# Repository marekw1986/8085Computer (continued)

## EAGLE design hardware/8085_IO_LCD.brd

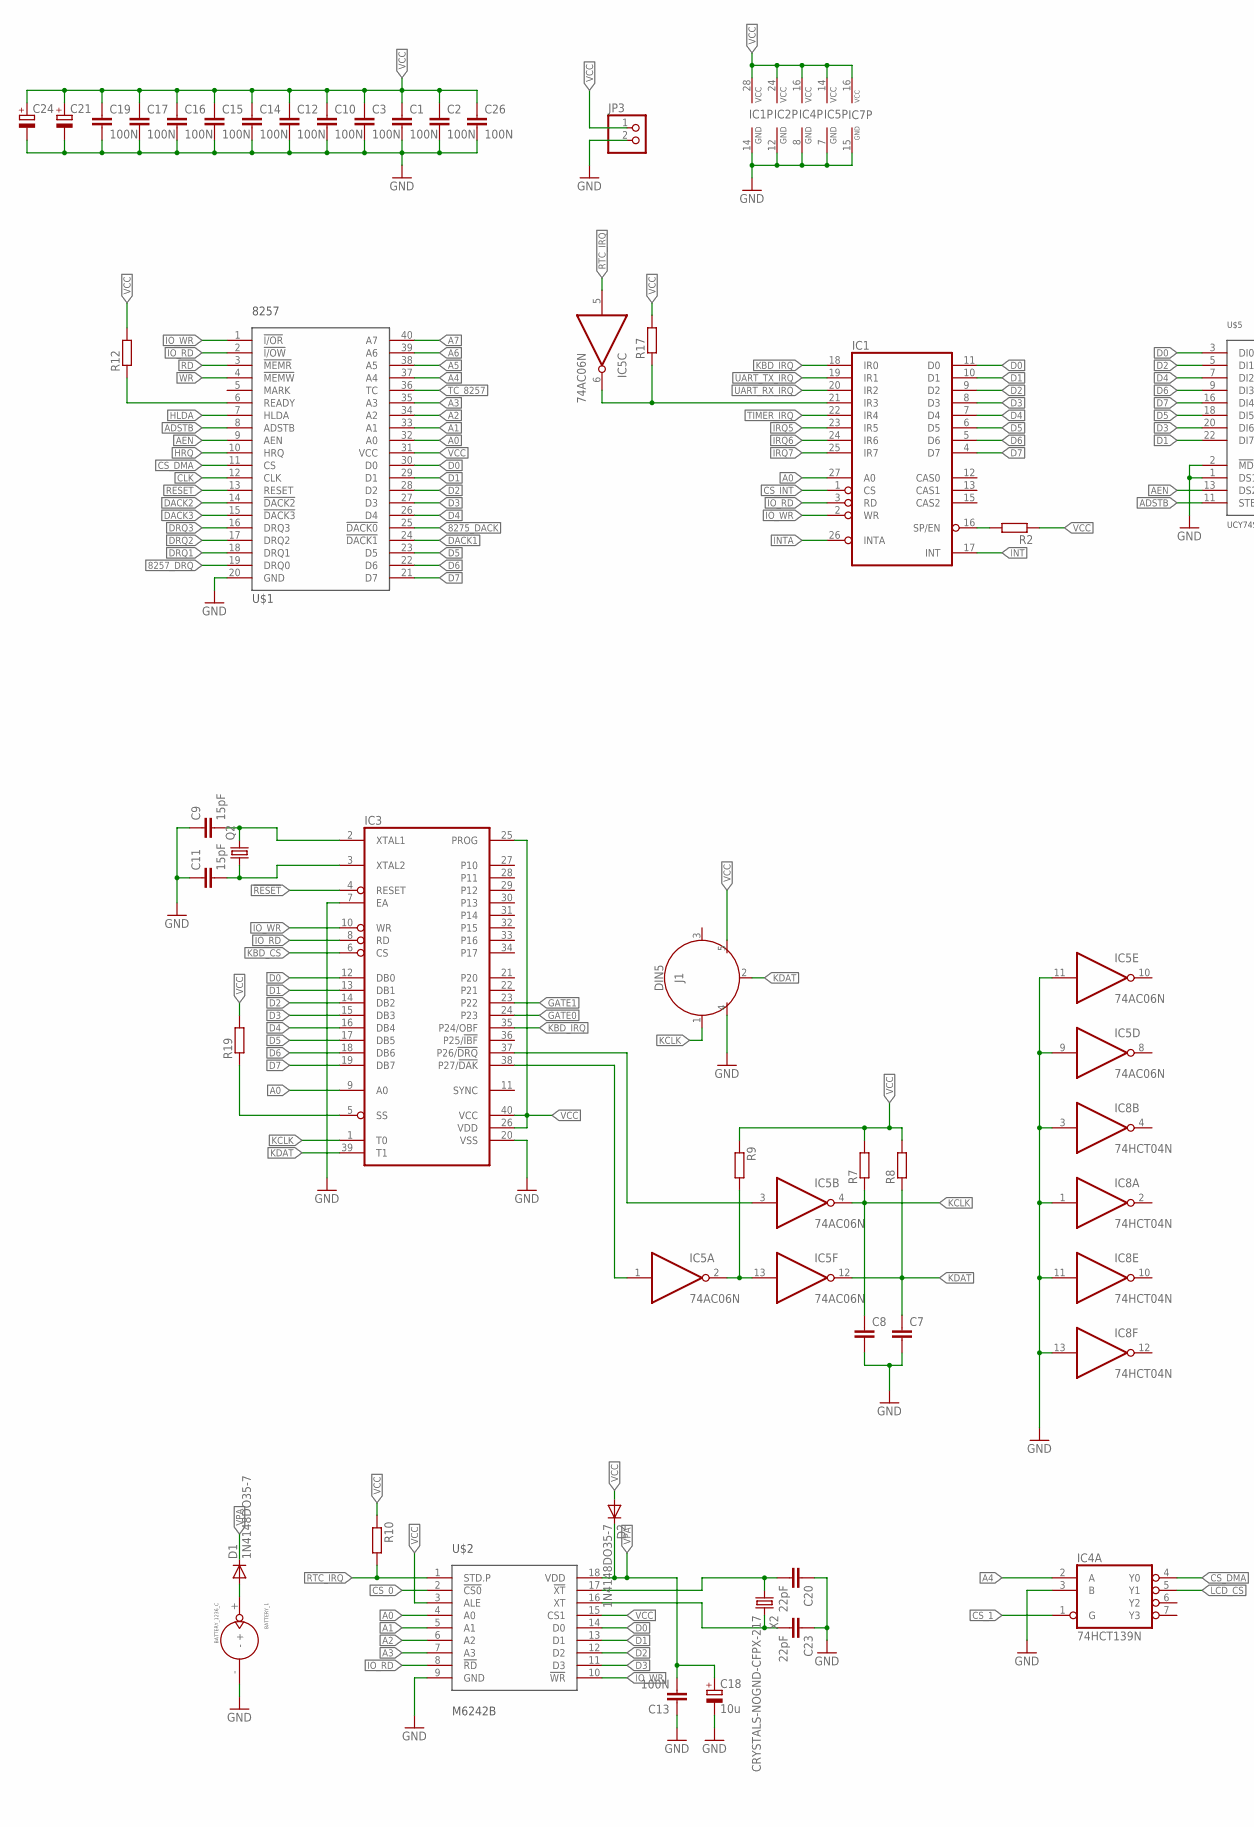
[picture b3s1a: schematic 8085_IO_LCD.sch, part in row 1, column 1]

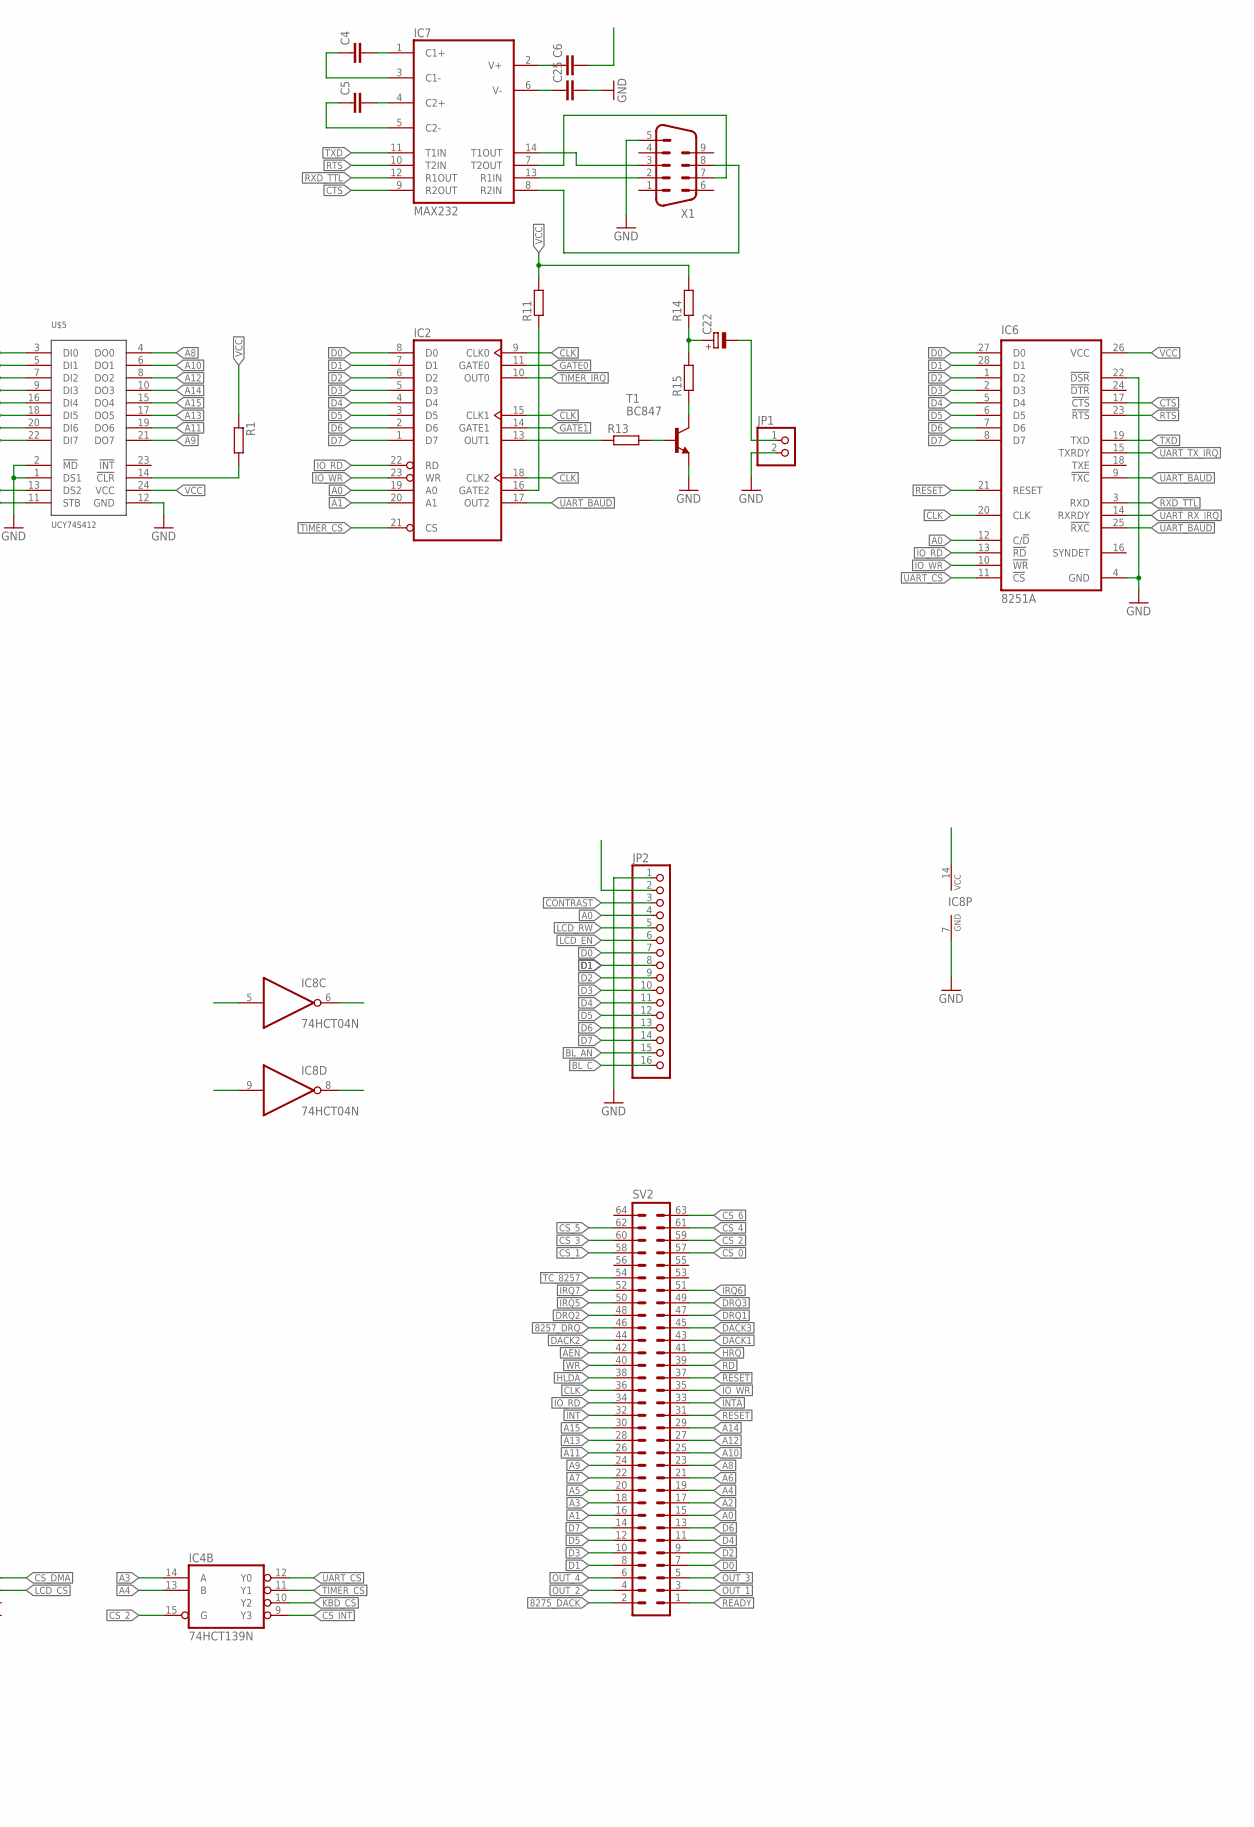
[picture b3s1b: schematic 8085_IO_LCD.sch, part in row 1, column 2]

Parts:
BATTERY_1: BATTERY_1236_C
C1, C3, C10, C12, C13, C14, C15, C16, C17, C19: 100N; C0603
C2: 100N; C1206
C4, C5, C6, C7, C8, C25: C-EUC0603; C0603
C9, C11: 15pF; C0603
C18: 10u; SMC_B
C20, C23: 22pF; C0603
C21: CPOL-EUE3.5-8; E3,5-8
C22: CPOL-EUE2-4; E2-4
C24: CPOL-EUSMCB; SMC_B
C26: 100N; C0805
D1, D2: 1N4148DO35-7; DO35-7
IC1: 8259A; DIL28-6
IC2: 8253; DIL24-6
IC3: UPI-8042AH; DIL40
IC4: 74HCT139N; DIL16
IC5: 74AC06N; DIL14
IC6: 8251A; DIL28-6
IC7: MAX232; DIL16
IC8: 74HCT04N; DIL14
J1: DIN5; DIN5-RA-PTH
JP1: PINHD-1X2; 1X02
JP2: PINHD-1X16; 1X16
JP3: PINHD-1X2/90; 1X02/90
Q2: CRYSTALHC49S; HC49/S
R1, R2, R9, R10, R11, R12, R13, R15: R-EU_R0603; R0603
R7, R14, R19: R-EU_0204/5; 0204/5
R8: R-EU_M0805; M0805
R17: R-EU_0204/7; 0204/7
SV2: ML64L
T1: BC847; SOT23
U$1: 8257; DIL40
U$2: M6242B; DIL18
U$5: UCY74S412; DIL24-6
X1: M09HP
X2: CRYSTALS-NOGND-CFPX-217; 3.2X1.5-2-PAD

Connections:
8257_DRQ: SV2.46, U$1.19 (DRQ0)
8275_DACK: SV2.2, U$1.25 (!DACK0)
!RESET: IC3.4 (RESET), SV2.37
A0: IC1.27 (A0), IC2.19 (A0), IC3.9 (A0), IC6.12 (C/!D), JP2.4, SV2.15, U$1.32 (A0), U$2.4 (A0)
A1: IC2.20 (A1), SV2.16, U$1.33 (A1), U$2.5 (A1)
A2: SV2.17, U$1.34 (A2), U$2.6 (A2)
A3: IC4.14 (A), SV2.18, U$1.35 (A3), U$2.7 (A3)
A4: IC4.2 (A), IC4.13 (B), SV2.19, U$1.37 (A4)
A5: SV2.20, U$1.38 (A5)
A6: SV2.21, U$1.39 (A6)
A7: SV2.22, U$1.40 (A7)
A8: SV2.23, U$5.4 (DO0)
A9: SV2.24, U$5.21 (DO7)
A10: SV2.25, U$5.6 (DO1)
A11: SV2.26, U$5.19 (DO6)
A12: SV2.27, U$5.8 (DO2)
A13: SV2.28, U$5.17 (DO5)
A14: SV2.29, U$5.10 (DO3)
A15: SV2.30, U$5.15 (DO4)
ADSTB: U$1.8 (ADSTB), U$5.11 (STB)
AEN: SV2.42, U$1.9 (AEN), U$5.13 (DS2)
BL_AN: JP2.15
BL_C: JP2.16
CLK: IC2.9 (CLK0), IC2.15 (CLK1), IC2.18 (CLK2), IC6.20 (CLK), SV2.36, U$1.12 (CLK)
CONTRAST: JP2.3
CS_0: SV2.57, U$2.2 (!CS0)
CS_1: IC4.1 (G), SV2.58
CS_2: IC4.15 (G), SV2.59
CS_3: SV2.60
CS_4: SV2.61
CS_5: SV2.62
CS_6: SV2.63
CS_DMA: IC4.4 (Y0), U$1.11 (CS)
CS_INT: IC1.1 (CS), IC4.9 (Y3)
CTS: IC6.17 (!CTS), IC7.9 (R2OUT)
D0: IC1.11 (D0), IC2.8 (D0), IC3.12 (DB0), IC6.27 (D0), JP2.7, SV2.7, U$1.30 (D0), U$2.14 (D0), U$5.3 (DI0)
D1: IC1.10 (D1), IC2.7 (D1), IC3.13 (DB1), IC6.28 (D1), JP2.8, SV2.8, U$1.29 (D1), U$2.13 (D1), U$5.22 (DI7)
D2: IC1.9 (D2), IC2.6 (D2), IC3.14 (DB2), IC6.1 (D2), JP2.9, SV2.9, U$1.28 (D2), U$2.12 (D2), U$5.5 (DI1)
D3: IC1.8 (D3), IC2.5 (D3), IC3.15 (DB3), IC6.2 (D3), JP2.10, SV2.10, U$1.27 (D3), U$2.11 (D3), U$5.20 (DI6)
D4: IC1.7 (D4), IC2.4 (D4), IC3.16 (DB4), IC6.5 (D4), JP2.11, SV2.11, U$1.26 (D4), U$5.7 (DI2)
D5: IC1.6 (D5), IC2.3 (D5), IC3.17 (DB5), IC6.6 (D5), JP2.12, SV2.12, U$1.23 (D5), U$5.18 (DI5)
D6: IC1.5 (D6), IC2.2 (D6), IC3.18 (DB6), IC6.7 (D6), JP2.13, SV2.13, U$1.22 (D6), U$5.9 (DI3)
D7: IC1.4 (D7), IC2.1 (D7), IC3.19 (DB7), IC6.8 (D7), JP2.14, SV2.14, U$1.21 (D7), U$5.16 (DI4)
DACK1: SV2.43, U$1.24 (!DACK1)
DACK2: SV2.44, U$1.14 (!DACK2)
DACK3: SV2.45, U$1.15 (!DACK3)
DRQ1: SV2.47, U$1.18 (DRQ1)
DRQ2: SV2.48, U$1.17 (DRQ2)
DRQ3: SV2.49, U$1.16 (DRQ3)
GATE0: IC2.11 (GATE0), IC3.24 (P23)
GATE1: IC2.14 (GATE1), IC3.23 (P22)
GATE2: IC2.16 (GATE2), R11.1
GND: BATTERY_1.-, C1.2, C2.2, C3.2, C7.2, C8.2, C9.1, C10.2, C11.1, C12.2, C13.1, C14.2, C15.2, C16.2, C17.2, C18.-, C19.2, C20.1, C21.-, C23.1, C24.-, C25.2, C26.2, IC1.14 (GND), IC2.12 (GND), IC3.7 (EA), IC3.20 (VSS), IC4.3 (B), IC4.8 (GND), IC5.7 (GND), IC5.9 (I), IC5.11 (I), IC6.4 (GND), IC6.22 (!DSR), IC7.15 (GND), IC8.1 (I), IC8.3 (I), IC8.7 (GND), IC8.11 (I), IC8.13 (I), J1.4, JP1.2, JP2.1, JP3.2, T1.2 (E), U$1.20 (GND), U$2.9 (GND), U$5.1 (DS1), U$5.2 (!MD), U$5.12 (GND), X1.5
HLDA: SV2.38, U$1.7 (HLDA)
HRQ: SV2.41, U$1.10 (HRQ)
INT: IC1.17 (INT), SV2.32
INTA: IC1.26 (INTA), SV2.33
IO_RD: IC1.3 (RD), IC2.22 (RD), IC3.8 (RD), IC6.13 (!RD), IC8.5 (I), SV2.34, U$1.2 (!I/OW), U$2.8 (!RD)
IO_WR: IC1.2 (WR), IC2.23 (WR), IC3.10 (WR), IC6.10 (!WR), SV2.35, U$1.1 (!I/OR), U$2.10 (!WR)
IRQ5: IC1.23 (IR5), SV2.50
IRQ6: IC1.24 (IR6), SV2.51
IRQ7: IC1.25 (IR7), SV2.52
KBD_CS: IC3.6 (CS), IC4.10 (Y2)
KBD_IRQ: IC1.18 (IR0), IC3.35 (P24/OBF)
KCLK: C8.1, IC3.1 (T0), IC5.4 (O), J1.1, R7.1
KDAT: C7.1, IC3.39 (T1), IC5.12 (O), J1.2, R8.1
LCD_CS: IC4.5 (Y1), IC8.9 (I)
LCD_EN: IC8.8 (O), JP2.6
LCD_RW: IC8.6 (O), JP2.5
unnamed: R1.2, U$5.14 (!CLR)
unnamed: IC1.16 (SP/EN), R2.2
unnamed: IC3.38 (P27/!DAK), IC5.1 (I)
unnamed: R12.1, U$1.6 (READY)
unnamed: IC2.13 (OUT1), R13.1
unnamed: IC7.7 (T2OUT), X1.7
unnamed: IC7.13 (R1IN), X1.2
unnamed: C4.2, IC7.1 (C1+)
unnamed: C5.2, IC7.4 (C2+)
unnamed: C5.1, IC7.5 (C2-)
unnamed: C4.1, IC7.3 (C1-)
unnamed: C6.1, IC7.2 (V+)
unnamed: C25.1, IC7.6 (V-)
unnamed: C9.2, IC3.2 (XTAL1), Q2.2
unnamed: C11.2, IC3.3 (XTAL2), Q2.1
unnamed: IC3.37 (P26/!DRQ), IC5.3 (I)
unnamed: IC7.14 (T1OUT), X1.3
unnamed: IC5.2 (O), IC5.13 (I), R9.2
unnamed: BATTERY_1.+, D1.A
unnamed: R13.2, T1.1 (B)
unnamed: R15.1, T1.3 (C)
unnamed: IC7.8 (R2IN), X1.8
unnamed: C22.-, JP1.1
unnamed: C22.+, R14.1, R15.2
unnamed: IC1.21 (IR3), IC5.6 (O), R17.1
unnamed: IC3.5 (SS), R19.1
OUT_1: SV2.3
OUT_2: SV2.4
OUT_3: SV2.5
OUT_4: SV2.6
RD: SV2.39, U$1.3 (!MEMR)
READY: SV2.1
RESET: IC6.21 (RESET), SV2.31, U$1.13 (RESET)
RTC_IRQ: IC5.5 (I), R10.2, U$2.1 (STD.P)
RTS: IC6.23 (!RTS), IC7.10 (T2IN)
RXD_TTL: IC6.3 (RXD), IC7.12 (R1OUT)
SOSCI: C20.2, U$2.17 (!XT), X2.1
SOSCO: C23.2, U$2.16 (XT), X2.2
TC_8257: SV2.54, U$1.36 (TC)
TIMER_CS: IC2.21 (CS), IC4.11 (Y1)
TIMER_IRQ: IC1.22 (IR4), IC2.10 (OUT0)
TXD: IC6.19 (TXD), IC7.11 (T1IN)
UART_BAUD: IC2.17 (OUT2), IC6.9 (!TXC), IC6.25 (!RXC)
UART_CS: IC4.12 (Y0), IC6.11 (!CS)
UART_RX_IRQ: IC1.20 (IR2), IC6.14 (RXRDY)
UART_TX_IRQ: IC1.19 (IR1), IC6.15 (TXRDY)
VCC: C1.1, C2.1, C3.1, C6.2, C10.1, C12.1, C14.1, C15.1, C16.1, C17.1, C19.1, C21.+, C24.+, C26.1, D2.A, IC1.28 (VCC), IC2.24 (VCC), IC3.25 (PROG), IC3.26 (VDD), IC3.40 (VCC), IC4.16 (VCC), IC5.14 (VCC), IC6.26 (VCC), IC7.16 (VCC), IC8.14 (VCC), J1.5, JP2.2, JP3.1, R1.1, R2.1, R7.2, R8.2, R9.1, R10.1, R11.2, R12.2, R14.2, R17.2, R19.2, U$1.31 (VCC), U$2.3 (ALE), U$2.15 (CS1), U$5.24 (VCC)
VPA: C13.2, C18.+, D1.C, D2.C, U$2.18 (VDD)
WR: SV2.40, U$1.4 (!MEMW)

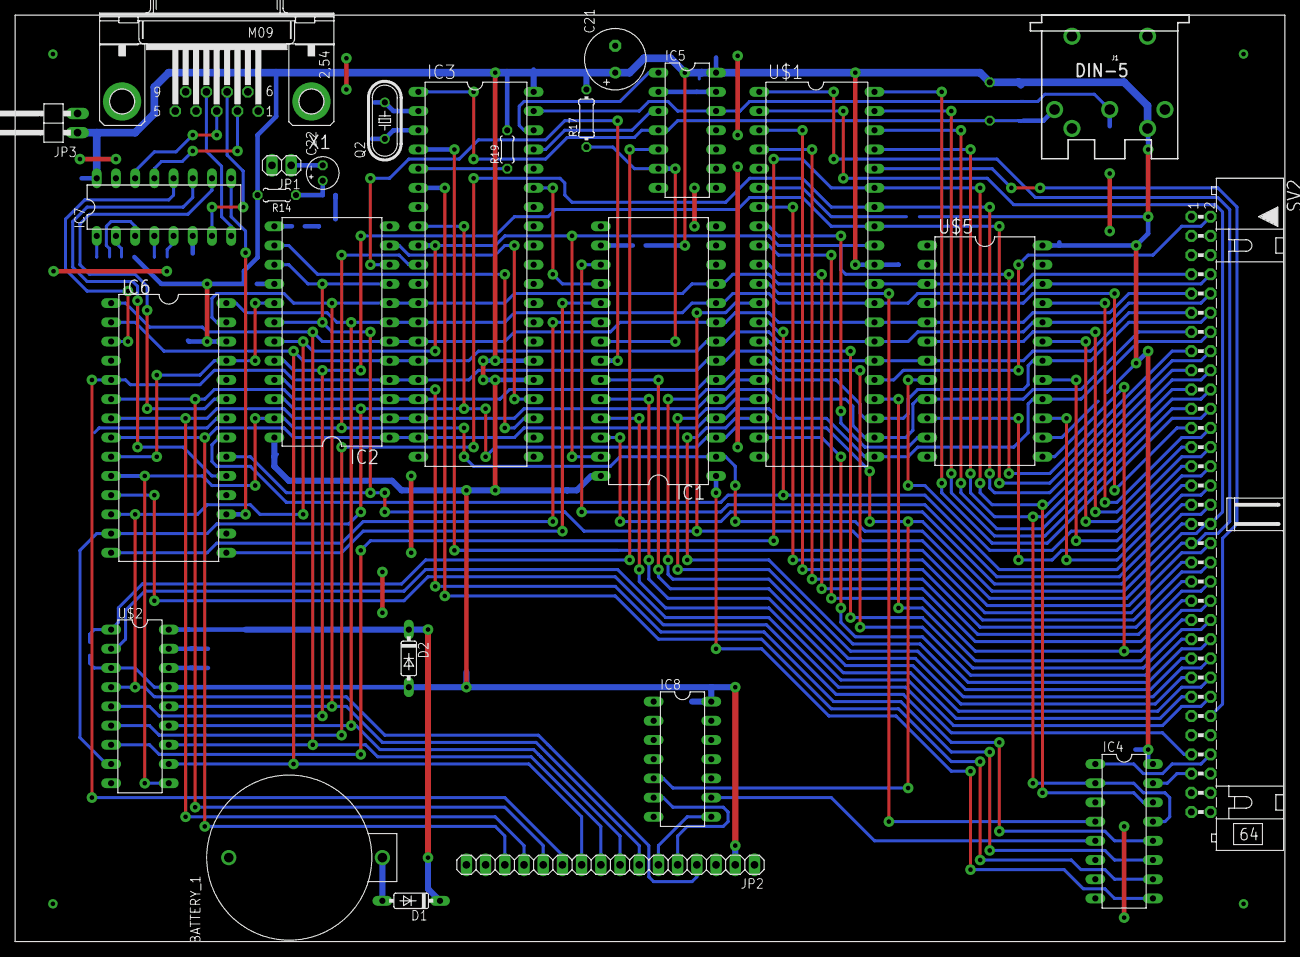
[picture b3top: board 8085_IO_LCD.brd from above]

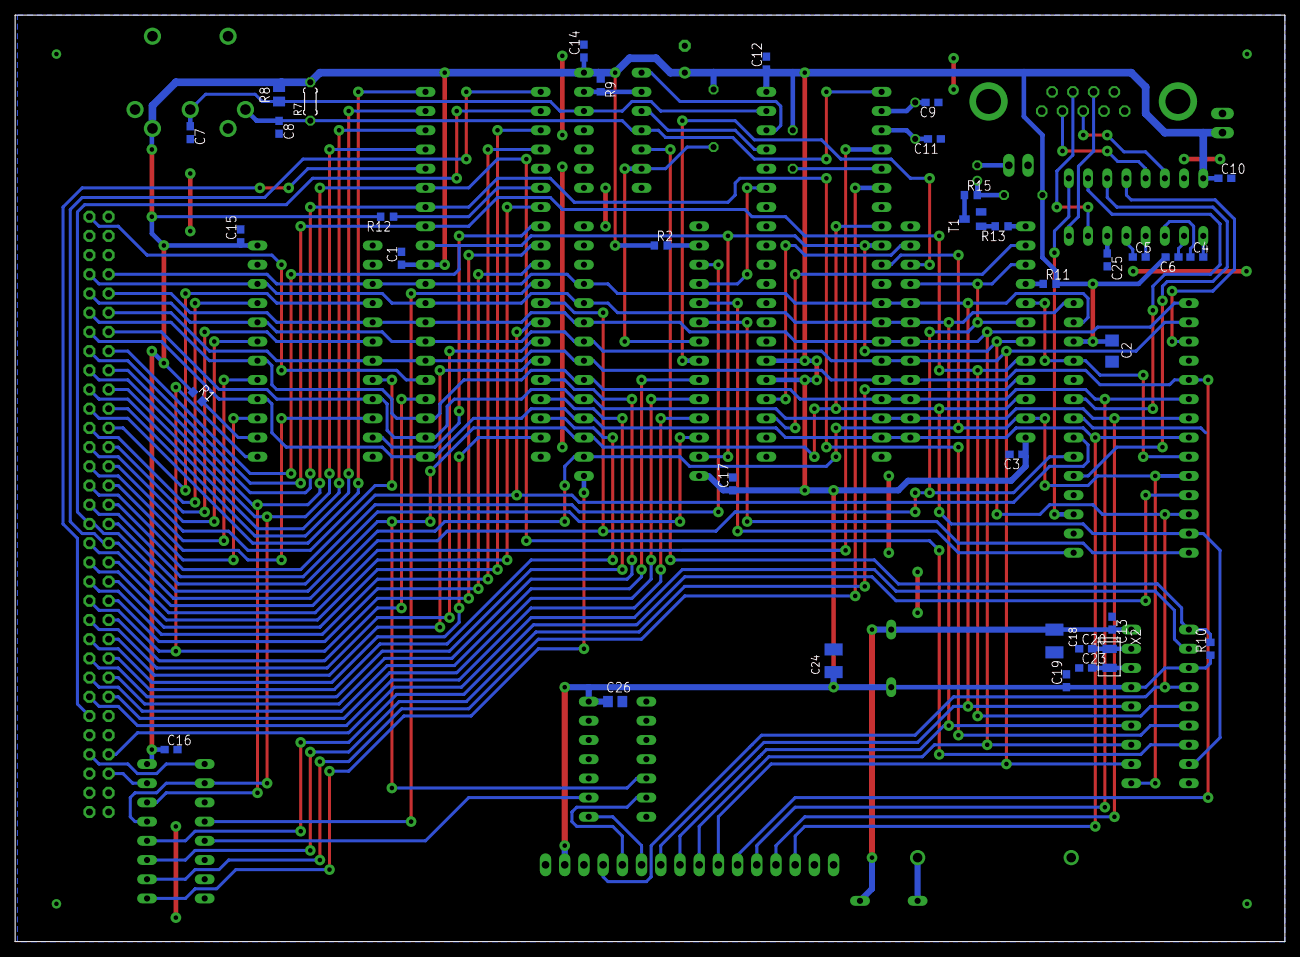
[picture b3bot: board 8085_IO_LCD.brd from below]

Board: 2 copper layers, 167.9 x 122.5 mm, 62 parts (36 on the bottom side), 106 nets.

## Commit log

2024-06-05 PCB updated
2024-07-17 Reset circuit simplified
2024-07-17 Minor optimizations
2024-08-03 PCB design upadted
2024-08-05 Minor PCB updates
2024-08-05 Minor update
2024-08-11 HW bug fixed, GAL added
2024-08-11 Minot HW fix
2024-08-11 Yet another HW issue fixed:
2024-08-11 Examplecode added
2024-08-11 Another update
2024-08-21 Code updated
2024-08-21 Test code updated
2024-09-02 IO board added
2024-09-18 LCD variant of IO board added
2024-12-26 Bug in PCB design fixed
2024-12-27 Local definitions removed from blink
2024-12-27 Blink updated
2024-12-27 uart test updated
2024-12-30 Bug in PCB board design fixed
2024-12-30 Addressed in definitions.asm fixed
2024-12-30 PS2 keyboar routines added to common
2024-12-30 Test works
2024-12-30 TinyBasic works
2024-12-30 CP/M bootloader added
2024-12-30 Get labels script added
2024-12-30 test.asm changed to test_uart.asm
2024-12-30 Test keyboard added
2024-12-30 Keyboard code removed from test_uart.asm
2025-01-01 8085 computer CP/M 2.2 bios version added (work in progress)
2025-01-01 Small changes
2025-01-02 GAL cleaned and modifed
2025-01-03 Small edit in CPM Makefile
2025-01-03 Exporting labels.asm generated during TinyBasic/Bootlader build to CPM directory
2025-01-03 Changes in cf.asm
2025-01-03 cf.asm moved to common directory
2025-01-03 Small changes in TinyBasic
2025-01-03 Small edits in test uart
2025-01-03 CF indicator LED added to CPU board
2025-01-05 IO address decoder gated with IOM signal
2025-01-05 minor PCB change
2025-01-05 Another minor PCB update
2025-01-17 Bugs in PCB board fixed
2025-01-19 CPU board updated
2025-01-23 Small changes in PCB design
2025-01-24 CP/M BIOS updated
2025-01-24 CPU board design updated. 7474 chip added to synchronize address decoders activity with ALE line.
2025-02-01 Minor changes in TinyBasic and CP/M bootloader
2025-02-01 CP/M rearanged in memory
2025-02-05 Shadowed rom option added
2025-02-05 Bootloader adjusted to new memory setting
2025-02-09 Rom shadowed version added, small changes in TB/Bootloader
2025-02-14 Getting CP/M source files automatically from github repository if they do not exist locally
2025-02-14 small changes in ROM shadowe version
2025-02-14 automatic downloading of filesystem content
2025-02-14 Reduced amount of data loaded at boot
2025-02-14 CP/M for shadowed version of hardware
2025-02-16 CP/M works with shadowed ROM version
2025-03-10 Caching CG reads (work in progress)
2025-03-10 CP/M BIOS optimized
2025-03-11 First experiments with BIOS write routine
2025-03-11 Minor optimization in CP/M bios read/write routines
2025-03-13 BIOS read refactored
2025-03-13 Write sector refactored
2025-03-13 CF read cache optimization
2025-03-13 CF write optimization while first sector of new track is being written
2025-03-13 Redundant code removed
2025-03-13 ROM shadowed version: dependancies from bootloader removed from BIOS. Some libraries removed to separate files to preserve space. Minor refactoring. Experiments with writing (not working for now).
2025-03-13 Writing fixed in shadowed ROM version of CP/M. Need to be improved.
2025-03-14 Fix in CP/M CF driver for shadowed ROM version
2025-03-14 CP/M BIOS updates ported from Z80
2025-03-14 New changes ported from Z80 computer project
2025-03-15 Multiple partition support
2025-03-15 Bug in CF card driver fixed
2025-03-16 Checking if bootloader loaded CP/M successfully
2025-03-17 Minor refactoring
2025-04-10 Shadower added
2025-04-19 Fix in classiv version GAL
2025-04-19 Tiny Basic in shadowed version ROM disabled
2025-04-19 Tiny Basic removed from ROM of version with ROM shadowing
2025-04-19 Missing file added
2025-04-19 Directory name changed
2025-04-19 Classiv version GAL fix
2025-04-19 Shadowed version GAL fix
2025-04-19 Changes from Z80 version backported
2025-09-11 MVI A, 00H replaced with XOR A to preserve memory and CPU cycles
2025-09-11 CPI 00H replaced with OR A
2025-09-11 Revert "MVI A, 00H replaced with XOR A to preserve memory and CPU cycles"
    This reverts commit 7e88d7f649f19ed6bf6bc259cda6de55ba1163e5.
2025-09-11 Revert "CPI 00H replaced with OR A"
    This reverts commit c14340f54a100b10e82b98b0e9cdf4dc6df40ed7.
2025-09-11 MVI A, 00H replaced with XRA A
2025-09-11 CPI 00H replaced with ORA A
2025-09-14 Bug in READ procedure fixed
2025-09-14 MVI A, 0 replaced wit XRA A in bios.asm
2025-09-16 Minor optimization
2025-09-17 Moving to ASL assembler and 8085undoc. In next step bootloader and CP/M bios will be optimized with undocummented 8085 instructions
